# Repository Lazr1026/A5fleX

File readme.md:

# A5fleX
A5fleX is a NAND/eMMC (in the form of a microSD card)/WiFi relocation FPC for Wii U motherboards that house the A5X processor.

For motherboards with the B1X processor, use the [cafeFlex](https://github.com/mackieks/cafeFlex/).

**A5fleX has not been tested**, it probably works but I have not confirmed so (yet). Designing hardware is free, testing it not so much..

## Credits
Lazr - Layout / routing  
YveltalGriffin - cafeFlex, the schematic of which was directly used here.

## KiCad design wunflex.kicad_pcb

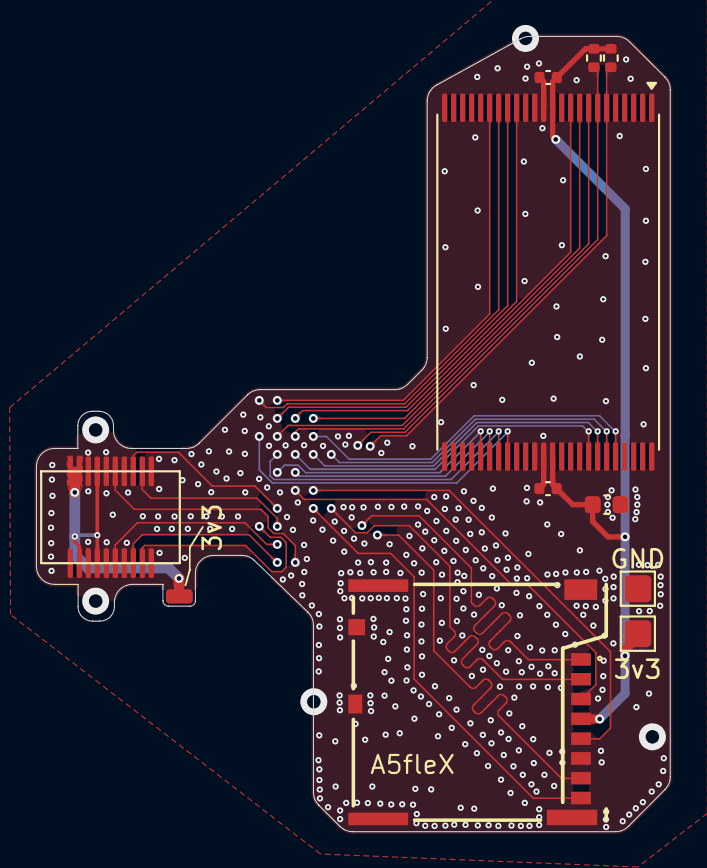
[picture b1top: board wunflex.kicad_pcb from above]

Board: 2 copper layers, 35.2 x 44.2 mm, 11 parts (0 on the bottom side), 4 nets.

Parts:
3v3, 3v3#2: TestPoint; TestPoint_Pad_1.5x1.5mm
C1, C2: 100nF; C_0402_1005Metric
C3: 4.7uF; C_0603_1608Metric
GND: TestPoint; TestPoint_Pad_1.5x1.5mm
J1: 2.4GHz Wi-Fi B2B; wificonn
J18: 503398-1892
R1, R2: 1K; R_0402_1005Metric
U1: K9K8G08U1D; TSOP-I-48_18.4x12mm_P0.5mm

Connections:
+3V3: 3v3.1 (1_1), 3v3#2.1 (1_1), C1.1, C2.1, C3.1, J1.7, J1.9, J1.11, J1.12, J1.14, J18.4 (VDD), R1.1, R2.1, U1.12 (VCC1), U1.37 (VCC2)
GND: C1.2, C2.2, C3.2, GND.1 (1_1), J1.1 (GND), J1.4, J1.6, J1.8, J1.13, J1.15, J1.17, J1.20, J18.6 (VSS), J18.9 (DETECT_LEVER), J18.10 (DETECT_SWITCH), J18.11, J18.12, J18.13, J18.14, U1.13 (VSS1), U1.36 (VSS2)
R/~B1: R1.2, U1.7 (R/~B1)
R/~B2: R2.2, U1.6 (R/~B2)
